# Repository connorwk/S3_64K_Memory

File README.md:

# S3_64K_Memory
64K replacement Memory board for the IBM System/3

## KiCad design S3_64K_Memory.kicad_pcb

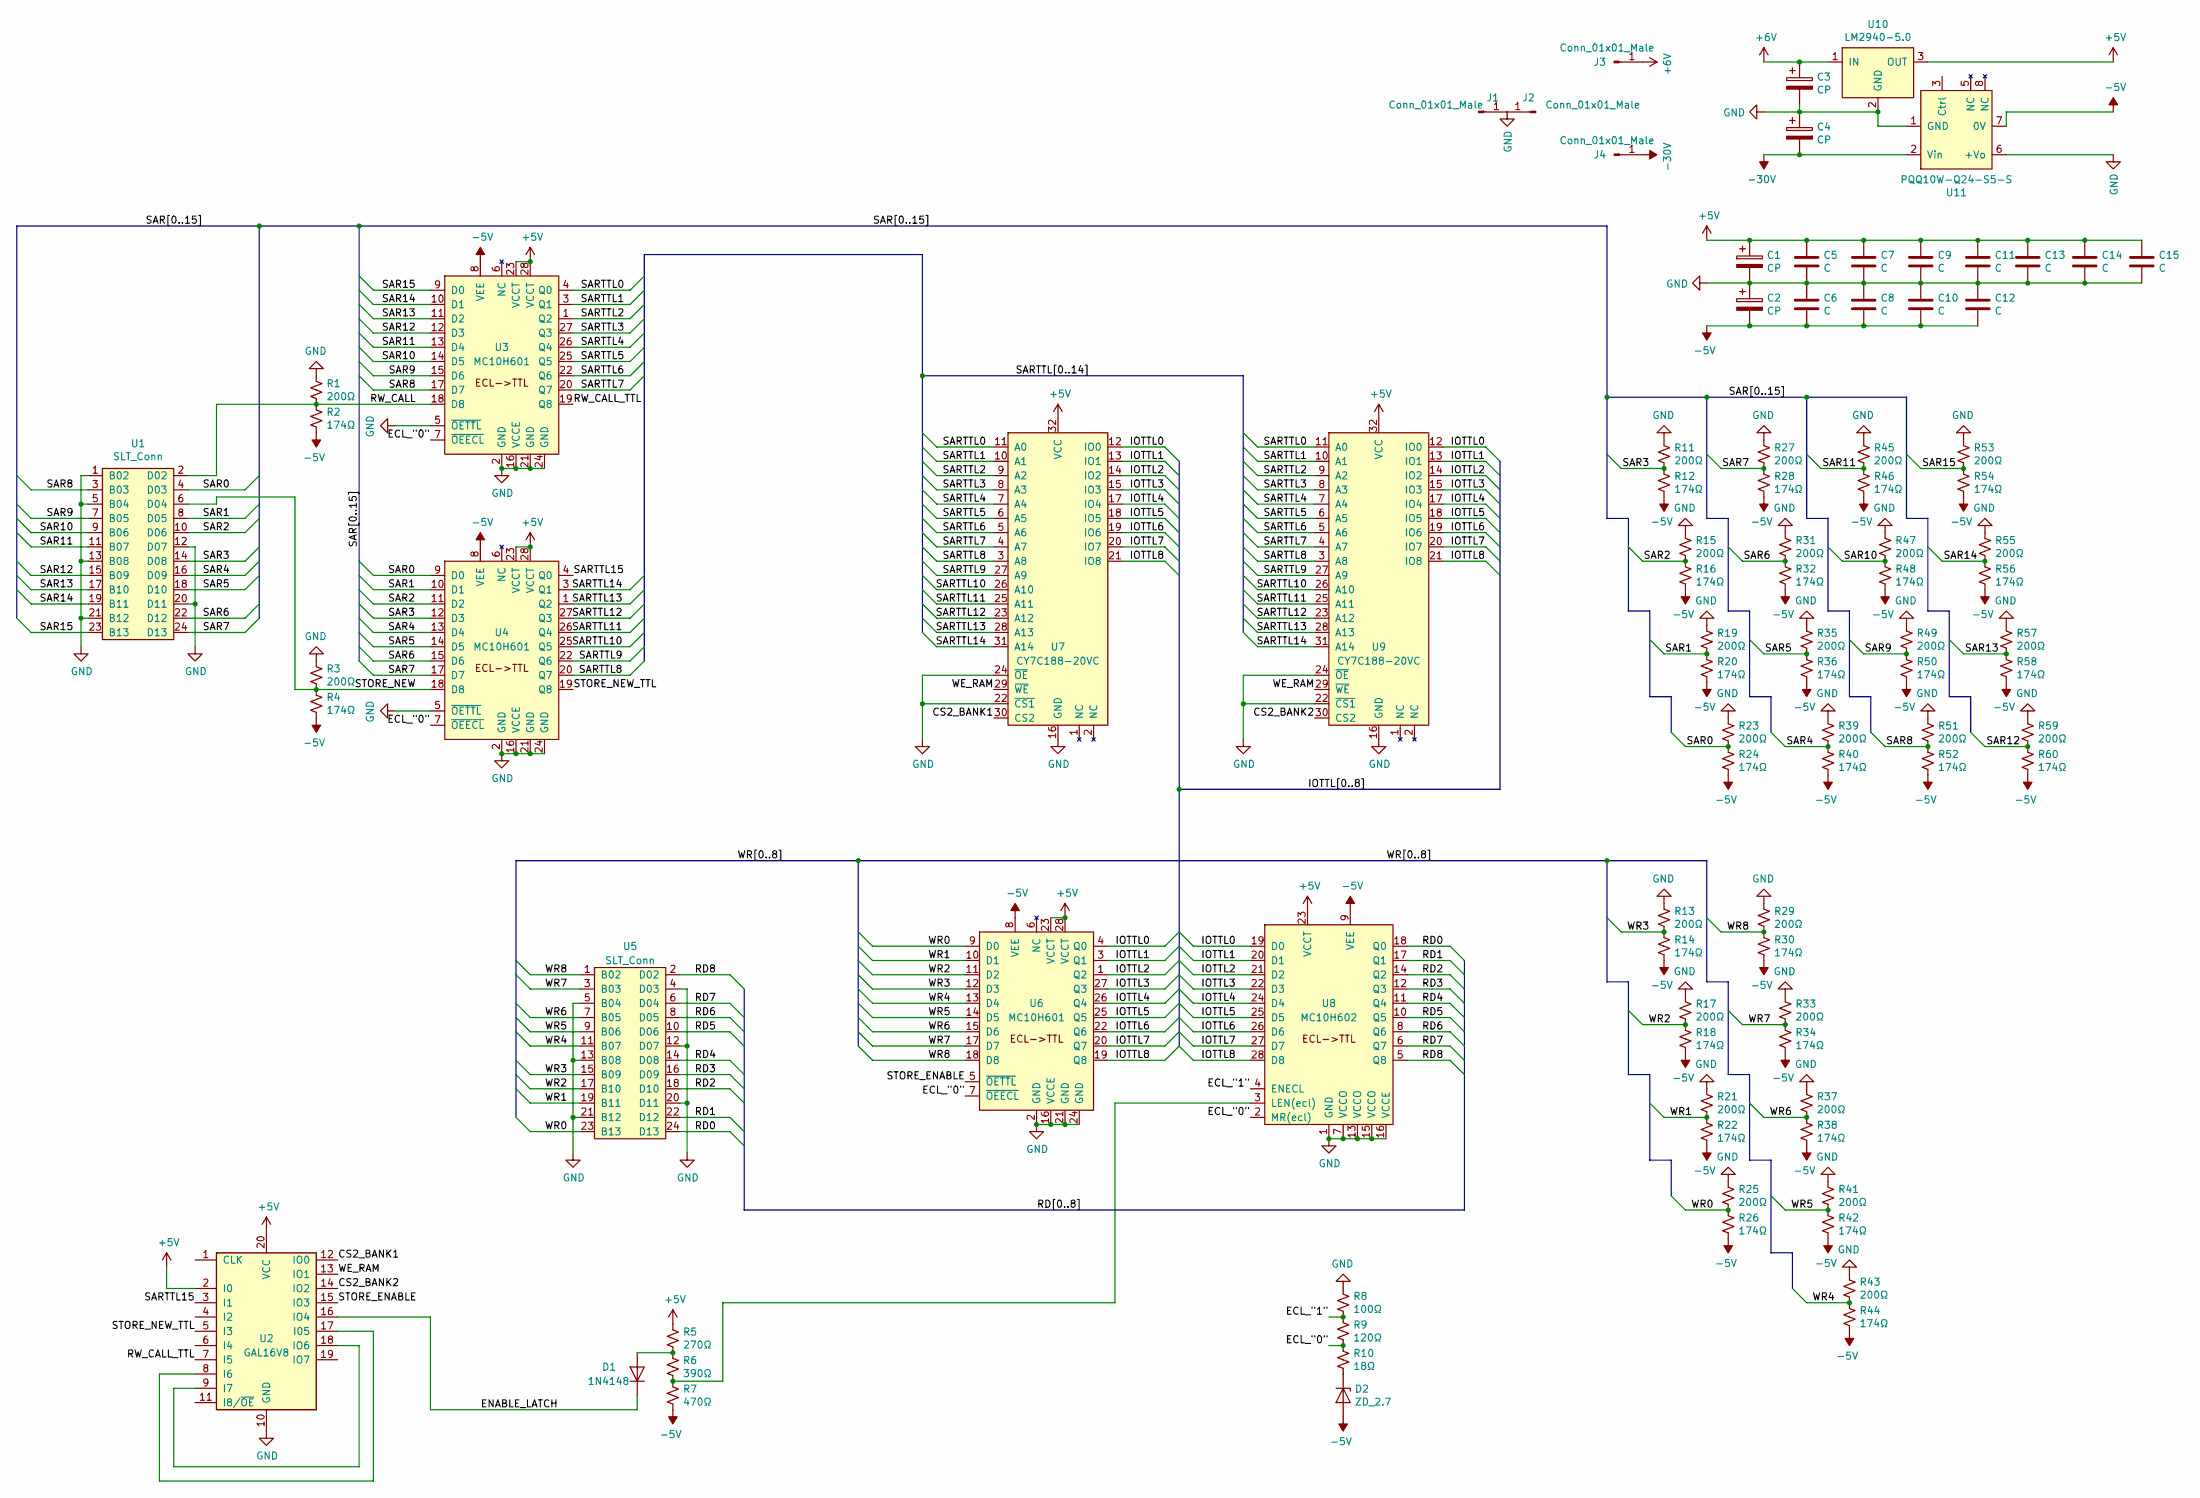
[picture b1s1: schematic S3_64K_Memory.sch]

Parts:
C1, C2, C3, C4: CP; CP_Radial_D5.0mm_P2.50mm
C5, C6, C7, C8, C9, C10, C11, C12, C13, C14, C15: C; C_Rect_L4.6mm_W2.0mm_P2.50mm_MKS02_FKP02
D1: 1N4148; D_DO-35_SOD27_P7.62mm_Horizontal
D2: ZD_2.7; D_DO-35_SOD27_P7.62mm_Horizontal
J1, J2, J3, J4: Conn_01x01_Male; PinHeader_1x01_P2.54mm_Vertical
R1, R3, R11, R13, R15, R17, R19, R21, R23, R25, R27, R29, R31, R33, R35, R37, R39, R41, R43, R45, R47, R49, R51, R53, R55, R57, R59: 200Ω; R_Axial_DIN0204_L3.6mm_D1.6mm_P2.54mm_Vertical
R2, R4, R12, R14, R16, R18, R20, R22, R24, R26, R28, R30, R32, R34, R36, R38, R40, R42, R44, R46, R48, R50, R52, R54, R56, R58, R60: 174Ω; R_Axial_DIN0204_L3.6mm_D1.6mm_P2.54mm_Vertical
R5: 270Ω; R_Axial_DIN0204_L3.6mm_D1.6mm_P7.62mm_Horizontal
R6: 390Ω; R_Axial_DIN0204_L3.6mm_D1.6mm_P7.62mm_Horizontal
R7: 470Ω; R_Axial_DIN0204_L3.6mm_D1.6mm_P7.62mm_Horizontal
R8: 100Ω; R_Axial_DIN0204_L3.6mm_D1.6mm_P7.62mm_Horizontal
R9: 120Ω; R_Axial_DIN0204_L3.6mm_D1.6mm_P7.62mm_Horizontal
R10: 18Ω; R_Axial_DIN0204_L3.6mm_D1.6mm_P7.62mm_Horizontal
U1, U5: SLT_Conn; PinHeader_2x12_P2.54mm_Vertical
U2: GAL16V8; DIP-20_W7.62mm_Socket_LongPads
U3, U4, U6: MC10H601; PLCC-28_THT-Socket
U7, U9: CY7C188-20VC; 32-SOJ-300mill
U8: MC10H602; PLCC-28_THT-Socket
U10: LM2940-5.0; TO-220-3_Horizontal_TabDown
U11: PQQ10W-Q24-S5-S

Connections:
+5V: C1.1, C5.1, C7.1, C9.1, C11.1, C13.1, C14.1, C15.1, R5.1, U2.2 (I0), U2.20 (VCC), U3.23 (VCCT), U3.28 (VCCT), U4.23 (VCCT), U4.28 (VCCT), U6.23 (VCCT), U6.28 (VCCT), U7.32 (VCC), U8.23 (VCCT), U9.32 (VCC), U10.3 (OUT)
+6V: C3.1, J3.1, U10.1 (IN)
-5V: C2.2, C6.2, C8.2, C10.2, C12.2, D2.2 (A), R2.2, R4.2, R7.2, R12.2, R14.2, R16.2, R18.2, R20.2, R22.2, R24.2, R26.2, R28.2, R30.2, R32.2, R34.2, R36.2, R38.2, R40.2, R42.2, R44.2, R46.2, R48.2, R50.2, R52.2, R54.2, R56.2, R58.2, R60.2, U3.8 (VEE), U4.8 (VEE), U6.8 (VEE), U8.9 (VEE), U11.7 (0V)
-30V: C4.2, J4.1, U11.2 (Vin)
/CS2_BANK1: U2.12 (IO0), U7.30 (CS2)
/CS2_BANK2: U2.14 (IO2), U9.30 (CS2)
/ENABLE_LATCH: D1.1 (K), U2.16 (IO4)
/IOTTL0: U6.4 (Q0), U7.12 (IO0), U8.19 (D0), U9.12 (IO0)
/IOTTL1: U6.3 (Q1), U7.13 (IO1), U8.20 (D1), U9.13 (IO1)
/IOTTL2: U6.1 (Q2), U7.14 (IO2), U8.21 (D2), U9.14 (IO2)
/IOTTL3: U6.27 (Q3), U7.15 (IO3), U8.22 (D3), U9.15 (IO3)
/IOTTL4: U6.26 (Q4), U7.17 (IO4), U8.24 (D4), U9.17 (IO4)
/IOTTL5: U6.25 (Q5), U7.18 (IO5), U8.25 (D5), U9.18 (IO5)
/IOTTL6: U6.22 (Q6), U7.19 (IO6), U8.26 (D6), U9.19 (IO6)
/IOTTL7: U6.20 (Q7), U7.20 (IO7), U8.27 (D7), U9.20 (IO7)
/IOTTL8: U6.19 (Q8), U7.21 (IO8), U8.28 (D8), U9.21 (IO8)
/RD0: U5.24 (D13), U8.18 (Q0)
/RD1: U5.22 (D12), U8.17 (Q1)
/RD2: U5.18 (D10), U8.14 (Q2)
/RD3: U5.16 (D09), U8.12 (Q3)
/RD4: U5.14 (D08), U8.11 (Q4)
/RD5: U5.10 (D06), U8.10 (Q5)
/RD6: U5.8 (D05), U8.8 (Q6)
/RD7: U5.6 (D04), U8.6 (Q7)
/RD8: U5.2 (D02), U8.5 (Q8)
/RW_CALL: R1.2, R2.1, U1.2 (D02), U3.18 (D8)
/RW_CALL_TTL: U2.7 (I5), U3.19 (Q8)
/SAR0: R23.2, R24.1, U1.4 (D03), U4.9 (D0)
/SAR1: R19.2, R20.1, U1.8 (D05), U4.10 (D1)
/SAR2: R15.2, R16.1, U1.10 (D06), U4.11 (D2)
/SAR3: R11.2, R12.1, U1.14 (D08), U4.12 (D3)
/SAR4: R39.2, R40.1, U1.16 (D09), U4.13 (D4)
/SAR5: R35.2, R36.1, U1.18 (D10), U4.14 (D5)
/SAR6: R31.2, R32.1, U1.22 (D12), U4.15 (D6)
/SAR7: R27.2, R28.1, U1.24 (D13), U4.17 (D7)
/SAR8: R51.2, R52.1, U1.3 (B03), U3.17 (D7)
/SAR9: R49.2, R50.1, U1.7 (B05), U3.15 (D6)
/SAR10: R47.2, R48.1, U1.9 (B06), U3.14 (D5)
/SAR11: R45.2, R46.1, U1.11 (B07), U3.13 (D4)
/SAR12: R59.2, R60.1, U1.15 (B09), U3.12 (D3)
/SAR13: R57.2, R58.1, U1.17 (B10), U3.11 (D2)
/SAR14: R55.2, R56.1, U1.19 (B11), U3.10 (D1)
/SAR15: R53.2, R54.1, U1.23 (B13), U3.9 (D0)
/SARTTL0: U3.4 (Q0), U7.11 (A0), U9.11 (A0)
/SARTTL1: U3.3 (Q1), U7.10 (A1), U9.10 (A1)
/SARTTL2: U3.1 (Q2), U7.9 (A2), U9.9 (A2)
/SARTTL3: U3.27 (Q3), U7.8 (A3), U9.8 (A3)
/SARTTL4: U3.26 (Q4), U7.7 (A4), U9.7 (A4)
/SARTTL5: U3.25 (Q5), U7.6 (A5), U9.6 (A5)
/SARTTL6: U3.22 (Q6), U7.5 (A6), U9.5 (A6)
/SARTTL7: U3.20 (Q7), U7.4 (A7), U9.4 (A7)
/SARTTL8: U4.20 (Q7), U7.3 (A8), U9.3 (A8)
/SARTTL9: U4.22 (Q6), U7.27 (A9), U9.27 (A9)
/SARTTL10: U4.25 (Q5), U7.26 (A10), U9.26 (A10)
/SARTTL11: U4.26 (Q4), U7.25 (A11), U9.25 (A11)
/SARTTL12: U4.27 (Q3), U7.23 (A12), U9.23 (A12)
/SARTTL13: U4.1 (Q2), U7.28 (A13), U9.28 (A13)
/SARTTL14: U4.3 (Q1), U7.31 (A14), U9.31 (A14)
/SARTTL15: U2.3 (I1), U4.4 (Q0)
/STORE_ENABLE: U2.15 (IO3), U6.5 (~OETTL)
/STORE_NEW: R3.2, R4.1, U1.6 (D04), U4.18 (D8)
/STORE_NEW_TTL: U2.5 (I3), U4.19 (Q8)
/WE_RAM: U2.13 (IO1), U7.29 (~WE), U9.29 (~WE)
/WR0: R25.2, R26.1, U5.23 (B13), U6.9 (D0)
/WR1: R21.2, R22.1, U5.19 (B11), U6.10 (D1)
/WR2: R17.2, R18.1, U5.17 (B10), U6.11 (D2)
/WR3: R13.2, R14.1, U5.15 (B09), U6.12 (D3)
/WR4: R43.2, R44.1, U5.11 (B07), U6.13 (D4)
/WR5: R41.2, R42.1, U5.9 (B06), U6.14 (D5)
/WR6: R37.2, R38.1, U5.7 (B05), U6.15 (D6)
/WR7: R33.2, R34.1, U5.3 (B03), U6.17 (D7)
/WR8: R29.2, R30.1, U5.1 (B02), U6.18 (D8)
GND: C1.2, C2.1, C3.2, C4.1, C5.2, C6.1, C7.2, C8.1, C9.2, C10.1, C11.2, C12.1, C13.2, C14.2, C15.2, J1.1, J2.1, R1.1, R3.1, R8.1, R11.1, R13.1, R15.1, R17.1, R19.1, R21.1, R23.1, R25.1, R27.1, R29.1, R31.1, R33.1, R35.1, R37.1, R39.1, R41.1, R43.1, R45.1, R47.1, R49.1, R51.1, R53.1, R55.1, R57.1, R59.1, U1.1 (B02), U1.5 (B04), U1.12 (D07), U1.13 (B08), U1.20 (D11), U1.21 (B12), U2.10 (GND), U3.2 (GND), U3.5 (~OETTL), U3.16 (VCCE), U3.21 (GND), U3.24 (GND), U4.2 (GND), U4.5 (~OETTL), U4.16 (VCCE), U4.21 (GND), U4.24 (GND), U5.4 (D03), U5.5 (B04), U5.12 (D07), U5.13 (B08), U5.20 (D11), U5.21 (B12), U6.2 (GND), U6.16 (VCCE), U6.21 (GND), U6.24 (GND), U7.16 (GND), U7.22 (~CS1), U7.24 (~OE), U8.1 (GND), U8.7 (VCCO), U8.13 (VCCO), U8.15 (VCCO), U8.16 (VCCE), U9.16 (GND), U9.22 (~CS1), U9.24 (~OE), U10.2 (GND), U11.1 (GND), U11.6 (+Vo)
unnamed: D1.2 (A), R5.2, R6.1
unnamed: D2.1 (K), R10.2
unnamed: R6.2, R7.1, U8.3 (LEN(ecl))
unnamed: U2.8 (I6), U2.17 (I05)
unnamed: U2.9 (I7), U2.18 (IO6)

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
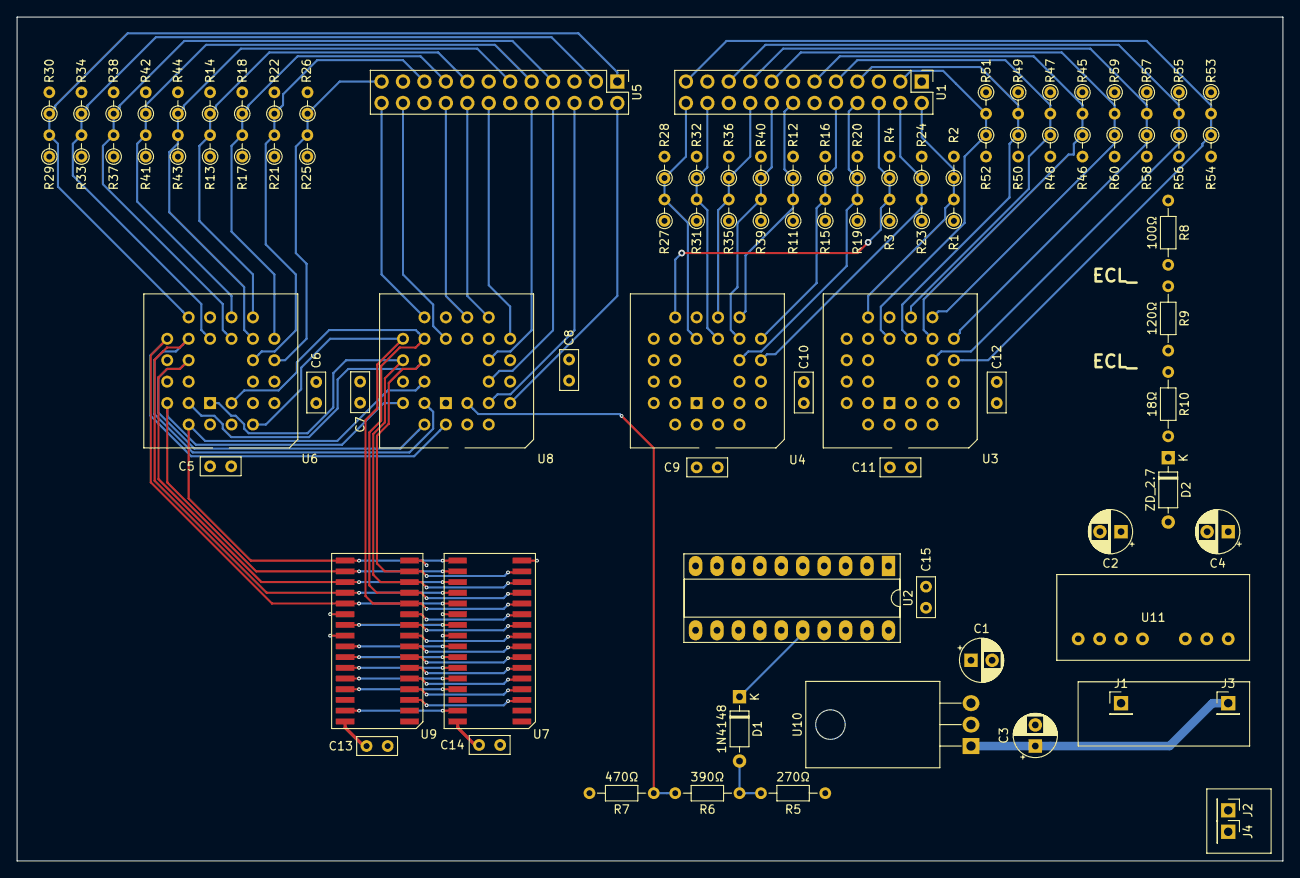
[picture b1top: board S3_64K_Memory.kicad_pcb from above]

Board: 4 copper layers, 150.0 x 100.0 mm, 92 parts (0 on the bottom side), 79 nets.

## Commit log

2021-04-13 Initial commit.
